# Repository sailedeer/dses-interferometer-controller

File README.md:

# dses-interferometer-controller
A repository for interferometer controller code, hardware, and simulations. 

See dses.science for more information on the Deep Space Exploration Society.

## System Overview

## Hardware
TODO

## Hardware Setup
To view/edit the KiCAD schematic, with KiCAD 6 open, go to Preferences -> Configure Paths, and add a new environment variable called "EWB" that points to dses-interferometer-controller\Hardware\lib.

## Raspberry Pi Setup

Install the 64 bit Raspberry Pi OS with Desktop. Configure the hostname and enable SSH with the right username and password.

``` bash
#Install the PyPy 3.9 Version of Conda Forge: Miniforge3-Linux-aarch64. 
#Use the default install directory, and allow it to initialize the base environment by default.
wget https://github.com/conda-forge/miniforge/releases/latest/download/Mambaforge-pypy3-Linux-aarch64.sh
sudo chmod +x Mambaforge-pypy3-Linux-aarch64.sh
./Mambaforge-pypy3-Linux-aarch64.sh

source ~/.bashrc #this will initialize the base env

mamba update python #update python

mamba create -n radioconda -c conda-forge -c ryanvolz --only-deps radioconda #Install radioconda 

conda activate radioconda

#Blacklist bad drivers
sudo ln -s $CONDA_PREFIX/etc/modprobe.d/rtl-sdr-blacklist.conf /etc/modprobe.d/radioconda-rtl-sdr-blacklist.conf
sudo modprobe -r $(cat $CONDA_PREFIX/etc/modprobe.d/rtl-sdr-blacklist.conf | sed -n -e 's/^blacklist //p')

#Udev rule
sudo ln -s $CONDA_PREFIX/lib/udev/rules.d/rtl-sdr.rules /etc/udev/rules.d/radioconda-rtl-sdr.rules
sudo udevadm control --reload
sudo udevadm trigger

#test the installation (plug in an RTL-SDR)
rtl_test
```

## Simulation Setup
Use Python 3.9.

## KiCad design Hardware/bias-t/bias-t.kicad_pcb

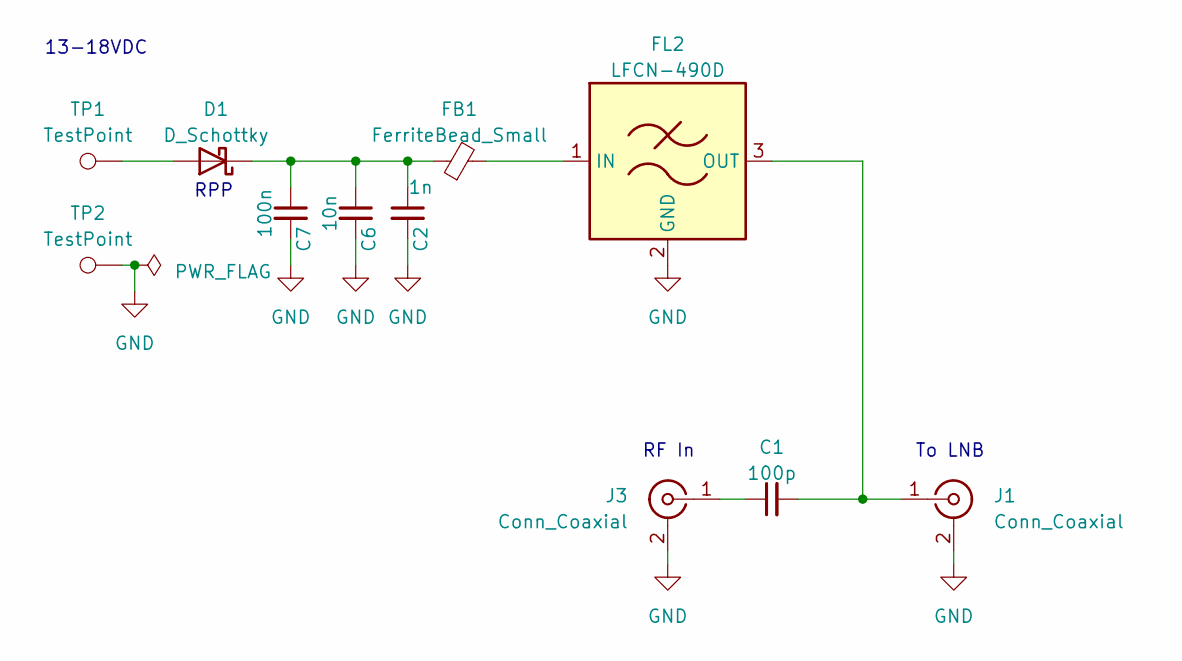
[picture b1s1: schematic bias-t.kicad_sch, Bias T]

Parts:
C1: 100p; C_0603_1608Metric
C2: 1n; C_0603_1608Metric
C6: 10n; C_0603_1608Metric
C7: 100n; C_0603_1608Metric
D1: D_Schottky; D_SOD-123
FB1: FerriteBead_Small; L_0805_2012Metric
FL2: LFCN-490D; Filter_Mini-Circuits_FV1206
J1, J3: Conn_Coaxial; SMA_Samtec_SMA-J-P-X-ST-EM1_EdgeMount
TP1, TP2: TestPoint; TestPoint_THTPad_4.0x4.0mm_Drill2.0mm

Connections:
GND: C2.2, C6.2, C7.2, FL2.2 (GND), FL2.4 (GND), J1.2 (Ext), J3.2 (Ext), TP2.1
unnamed: D1.2 (A), TP1.1
unnamed: C2.1, C6.1, C7.1, D1.1 (K), FB1.1
unnamed: FB1.2, FL2.1 (IN)
unnamed: C1.2, FL2.3 (OUT), J1.1 (In)
unnamed: C1.1, J3.1 (In)

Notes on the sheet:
RF In
To LNB
13-18VDC
RPP

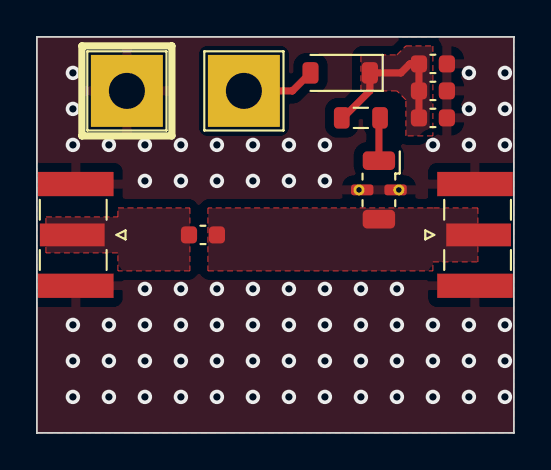
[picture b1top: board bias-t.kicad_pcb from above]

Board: 2 copper layers, 26.5 x 22.0 mm, 11 parts (0 on the bottom side), 6 nets.

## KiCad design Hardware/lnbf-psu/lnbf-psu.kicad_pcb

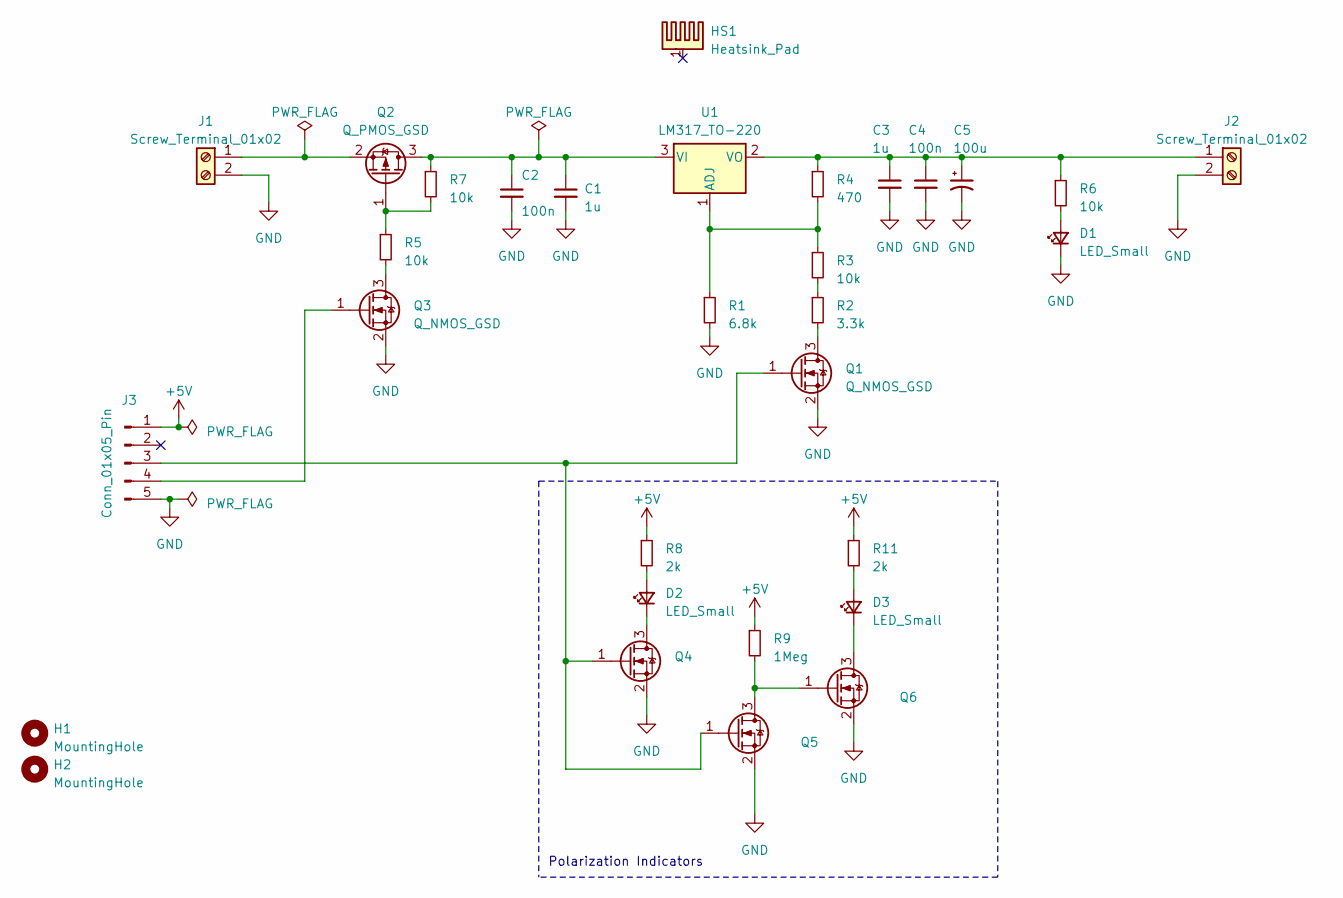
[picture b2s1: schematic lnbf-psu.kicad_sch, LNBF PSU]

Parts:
C1, C3: 1u; C_0805_2012Metric
C2, C4: 100n; C_1206_3216Metric
C5: 100u; CP_Elec_10x10
D1, D2, D3: LED_Small; LED_0805_2012Metric
H1, H2: MountingHole; MountingHole_2.7mm_M2.5
HS1: Heatsink_Pad; TO-220-RS-Heatsink
J1, J2: Screw_Terminal_01x02; TerminalBlock_Phoenix_MKDS-3-2-5.08_1x02_P5.08mm_Horizontal
J3: Conn_01x05_Pin; PinHeader_1x05_P2.54mm_Vertical
Q1, Q3, Q4, Q5, Q6: Q_NMOS_GSD; SOT-23
Q2: Q_PMOS_GSD; TO-252-2
R1: 6.8k; R_0603_1608Metric
R2: 3.3k; R_0603_1608Metric
R3, R5, R6, R7: 10k; R_0603_1608Metric
R4: 470; R_0603_1608Metric
R8, R11: 2k; R_0603_1608Metric
R9: 1Meg; R_0603_1608Metric
U1: LM317_TO-220; TO-220F-3_Horizontal_TabDown

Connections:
+5V: J3.1, R8.1, R9.1, R11.1
GND: C1.2, C2.2, C3.2, C4.2, C5.2, D1.1 (K), J1.2, J2.2, J3.5, Q1.2 (S), Q3.2 (S), Q4.2 (S), Q5.2 (S), Q6.2 (S), R1.2
unnamed: D1.2 (A), R6.2
unnamed: D2.2 (A), R8.2
unnamed: D2.1 (K), Q4.3 (D)
unnamed: D3.2 (A), R11.2
unnamed: D3.1 (K), Q6.3 (D)
unnamed: J1.1, Q2.2 (S)
unnamed: C3.1, C4.1, C5.1, J2.1, R4.1, R6.1, U1.2 (VO)
unnamed: J3.3, Q1.1 (G), Q4.1 (G), Q5.1 (G)
unnamed: J3.4, Q3.1 (G)
unnamed: Q1.3 (D), R2.2
unnamed: C1.1, C2.1, Q2.3 (D), R7.1, U1.3 (VI)
unnamed: Q2.1 (G), R5.1, R7.2
unnamed: Q3.3 (D), R5.2
unnamed: Q5.3 (D), Q6.1 (G), R9.2
unnamed: R2.1, R3.2
unnamed: R1.1, R3.1, R4.2, U1.1 (ADJ)

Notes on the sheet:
Polarization Indicators

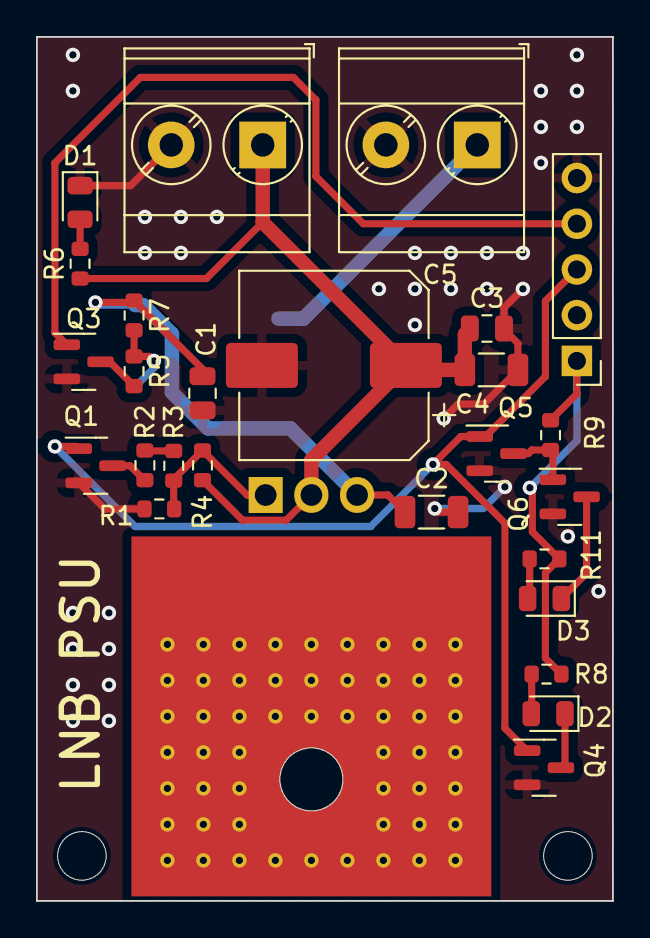
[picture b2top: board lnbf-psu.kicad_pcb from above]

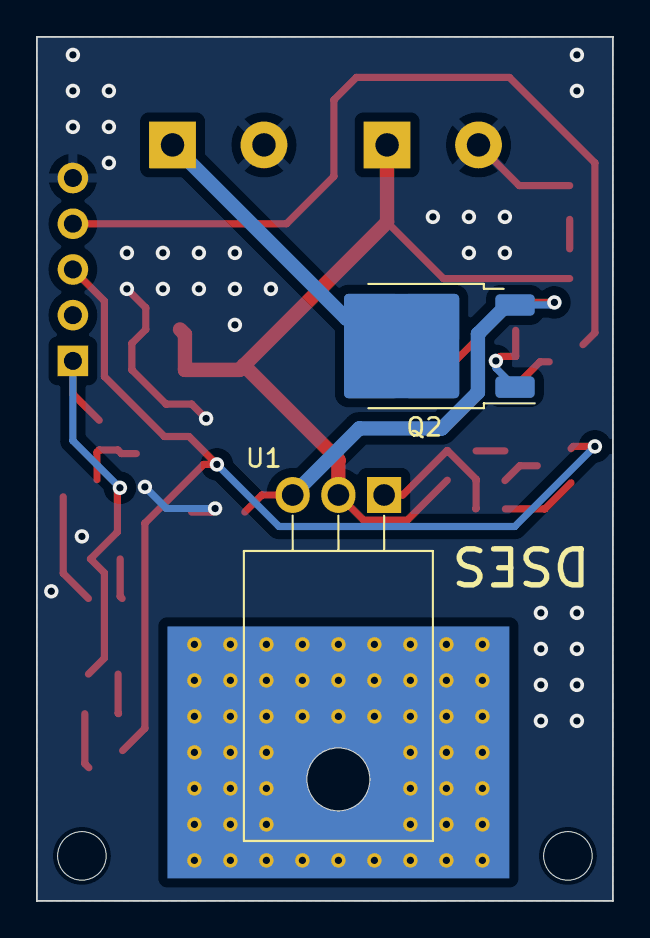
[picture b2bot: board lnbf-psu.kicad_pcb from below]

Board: 2 copper layers, 32.0 x 48.0 mm, 31 parts (2 on the bottom side), 18 nets.

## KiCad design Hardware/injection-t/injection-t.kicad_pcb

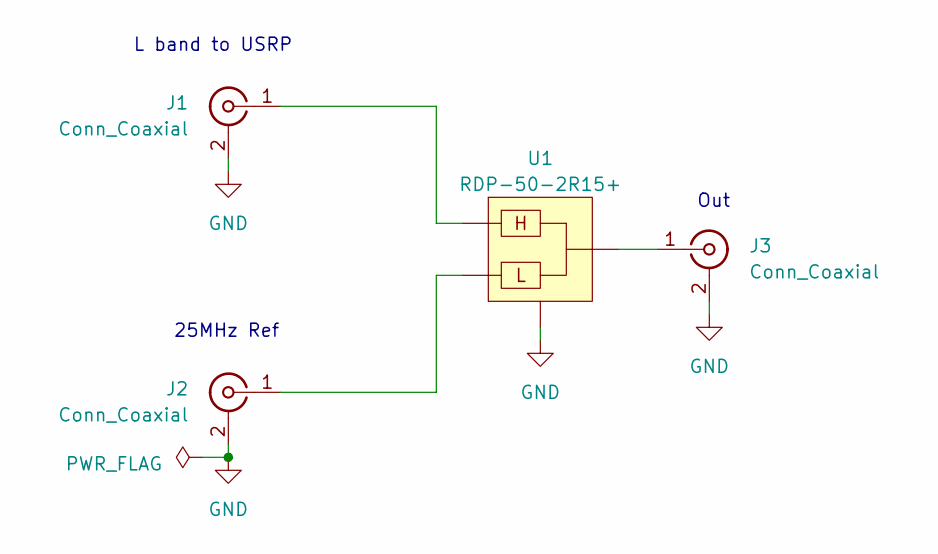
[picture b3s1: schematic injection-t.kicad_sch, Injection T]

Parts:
J1, J2, J3: Conn_Coaxial; SMA_Samtec_SMA-J-P-X-ST-EM1_EdgeMount
U1: RDP-50-2R15+; Mini-Circuits_CK605_LandPatternPL-012

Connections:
GND: J1.2 (Ext), J2.2 (Ext), J3.2 (Ext), U1.1 (GND), U1.3 (GND), U1.4 (GND), U1.5 (GND), U1.6 (GND), U1.7 (GND), U1.8 (GND), U1.9 (GND), U1.11 (GND), U1.12 (GND), U1.13 (GND), U1.15 (GND), U1.16 (GND)
unnamed: J1.1 (In), U1.10 (HI)
unnamed: J2.1 (In), U1.14 (LO)
unnamed: J3.1 (In), U1.2 (COM)

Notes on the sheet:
25MHz Ref
L band to USRP
Out

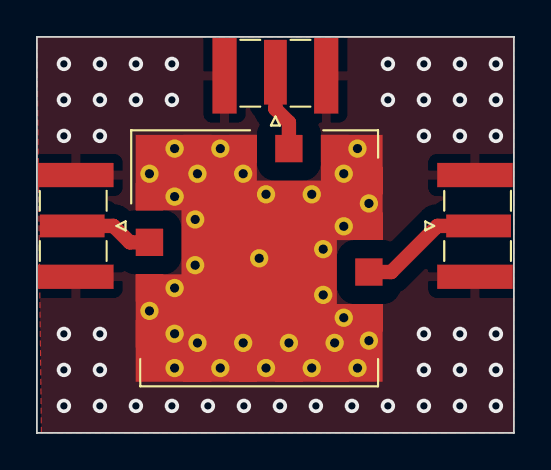
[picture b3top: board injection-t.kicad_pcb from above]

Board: 2 copper layers, 26.5 x 22.0 mm, 4 parts (0 on the bottom side), 4 nets.

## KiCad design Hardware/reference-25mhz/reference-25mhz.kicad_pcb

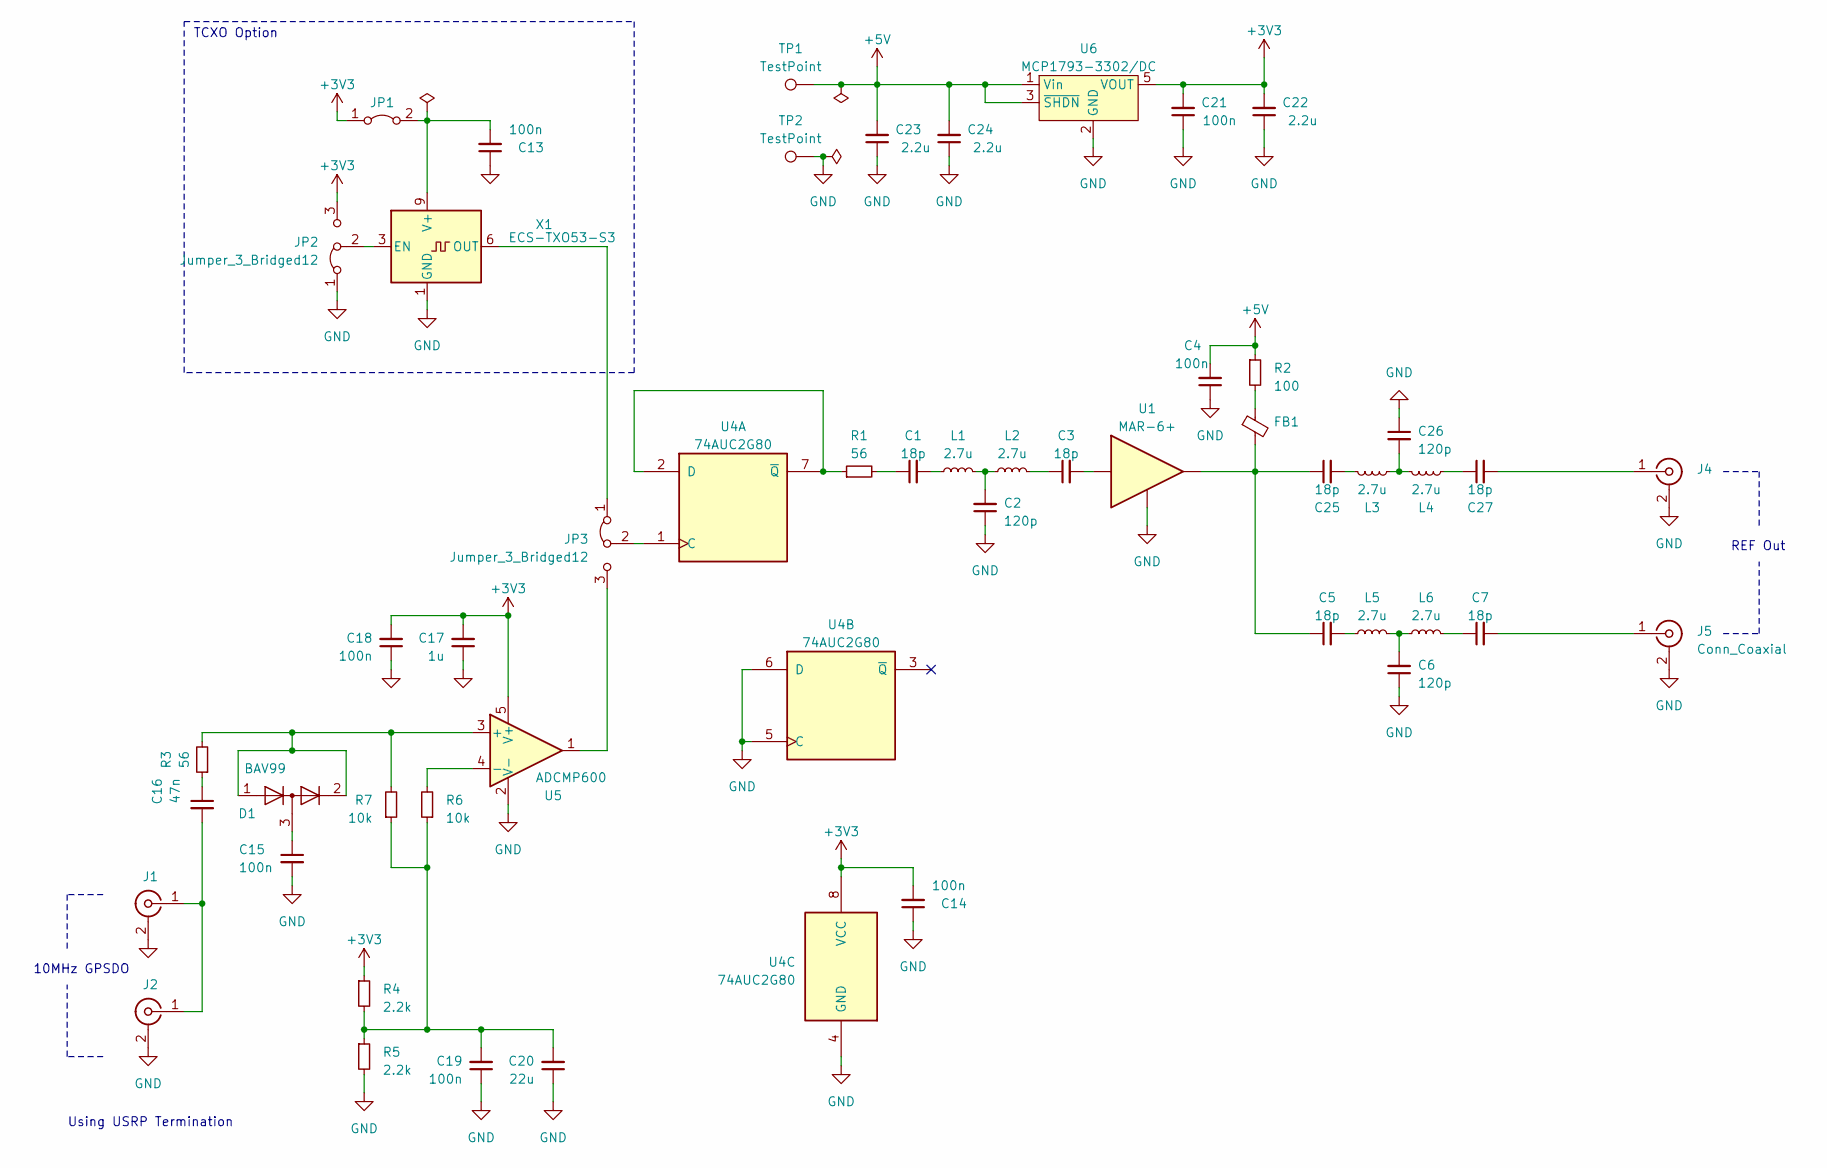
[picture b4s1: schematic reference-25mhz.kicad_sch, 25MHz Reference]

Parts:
C1, C3, C5, C7, C25, C27: 18p; C_0603_1608Metric
C2, C6, C26: 120p; C_0603_1608Metric
C4, C13, C14, C15, C18, C19, C21: 100n; C_1206_3216Metric
C16: 47n; C_0603_1608Metric
C17: 1u; C_0603_1608Metric
C20: 22u; C_0805_2012Metric
C22, C23, C24: 2.2u; C_0603_1608Metric
D1: BAV99; SOT-23
FB1: FerriteBead_Small; L_0805_2012Metric
J1, J2, J4, J5: Conn_Coaxial; SMA_Samtec_SMA-J-P-X-ST-EM1_EdgeMount
JP1: Jumper_2_Bridged; R_0603_1608Metric
JP2: Jumper_3_Bridged12; SolderJumper-3_P1.3mm_Bridged12_Pad1.0x1.5mm
JP3: Jumper_3_Bridged12; SolderJumper-3_P1.3mm_Open_Pad1.0x1.5mm
L1, L2, L3, L4, L5, L6: 2.7u; L_0603_1608Metric
R1, R3: 56; R_0603_1608Metric
R2: 100; R_0603_1608Metric
R4, R5: 2.2k; R_0603_1608Metric
R6, R7: 10k; R_0603_1608Metric
TP1, TP2: TestPoint; TestPoint_THTPad_2.5x2.5mm_Drill1.2mm
U1: MAR-6+; MINICIRCUITS_VV105
U4: 74AUC2G80; VSSOP-8_2.3x2mm_P0.5mm
U5: ADCMP600; SOT-353_SC-70-5
U6: MCP1793-3302/DC; SOT-23-5
X1: ECS-TXO53-S3

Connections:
+3V3: C14.2, C17.2, C18.2, C21.2, C22.2, JP1.1 (A), JP2.3 (B), R4.1, U4.8 (VCC), U5.5 (V+), U6.5 (VOUT)
+5V: C4.2, C23.2, C24.2, R2.1, TP1.1, U6.1 (Vin), U6.3 (~SHDN)
GND: C2.1, C4.1, C6.1, C13.1, C14.1, C15.2, C17.1, C18.1, C19.1, C20.1, C21.1, C22.1, C23.1, C24.1, C26.1, J1.2 (Ext), J2.2 (Ext), J4.2 (Ext), J5.2 (Ext), JP2.1 (A), R5.2, TP2.1, U1.2 (GND), U1.4 (GND), U4.4 (GND), U4.5 (C), U4.6 (D), U5.2 (V-), U6.2 (GND), X1.1 (GND), X1.4 (GND)
unnamed: C13.2, JP1.2 (B), X1.9 (V+)
unnamed: C1.1, R1.2
unnamed: C1.2, L1.1
unnamed: C2.2, L1.2, L2.1
unnamed: C3.1, L2.2
unnamed: C5.2, L5.1
unnamed: C6.2, L5.2, L6.1
unnamed: C7.1, L6.2
unnamed: C15.1, D1.3 (K)
unnamed: C16.1, R3.1
unnamed: C19.2, C20.2, R4.2, R5.1, R6.1, R7.1
unnamed: C25.2, L3.1
unnamed: C26.2, L3.2, L4.1
unnamed: C27.1, L4.2
unnamed: D1.1 (K), D1.2 (A), R3.2, R7.2, U5.3 (+)
unnamed: FB1.1, R2.2
unnamed: C16.2, J1.1 (In), J2.1 (In)
unnamed: C27.2, J4.1 (In)
unnamed: C7.2, J5.1 (In)
unnamed: JP2.2 (C), X1.3 (EN)
unnamed: JP3.1 (A), X1.6 (OUT)
unnamed: JP3.3 (B), U5.1
unnamed: JP3.2 (C), U4.1 (C)
unnamed: C3.2, U1.1 (RFIN)
unnamed: C5.1, C25.1, FB1.2, U1.3 (RFOUT)
unnamed: R1.1, U4.2 (D), U4.7 (~Q)
unnamed: R6.2, U5.4 (-)

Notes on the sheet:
REF Out
Using USRP Termination
10MHz GPSDO
TCXO Option

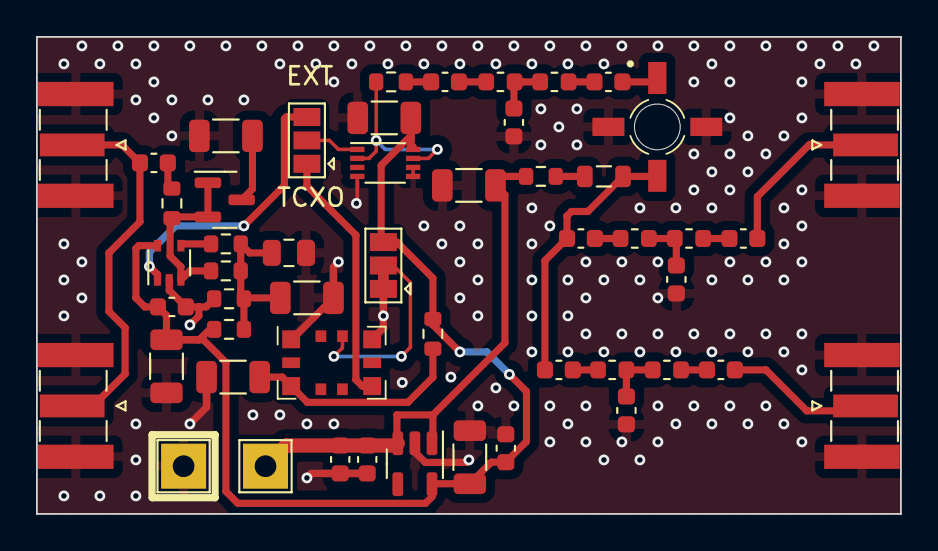
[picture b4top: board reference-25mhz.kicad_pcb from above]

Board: 2 copper layers, 48.0 x 26.5 mm, 51 parts (0 on the bottom side), 30 nets.

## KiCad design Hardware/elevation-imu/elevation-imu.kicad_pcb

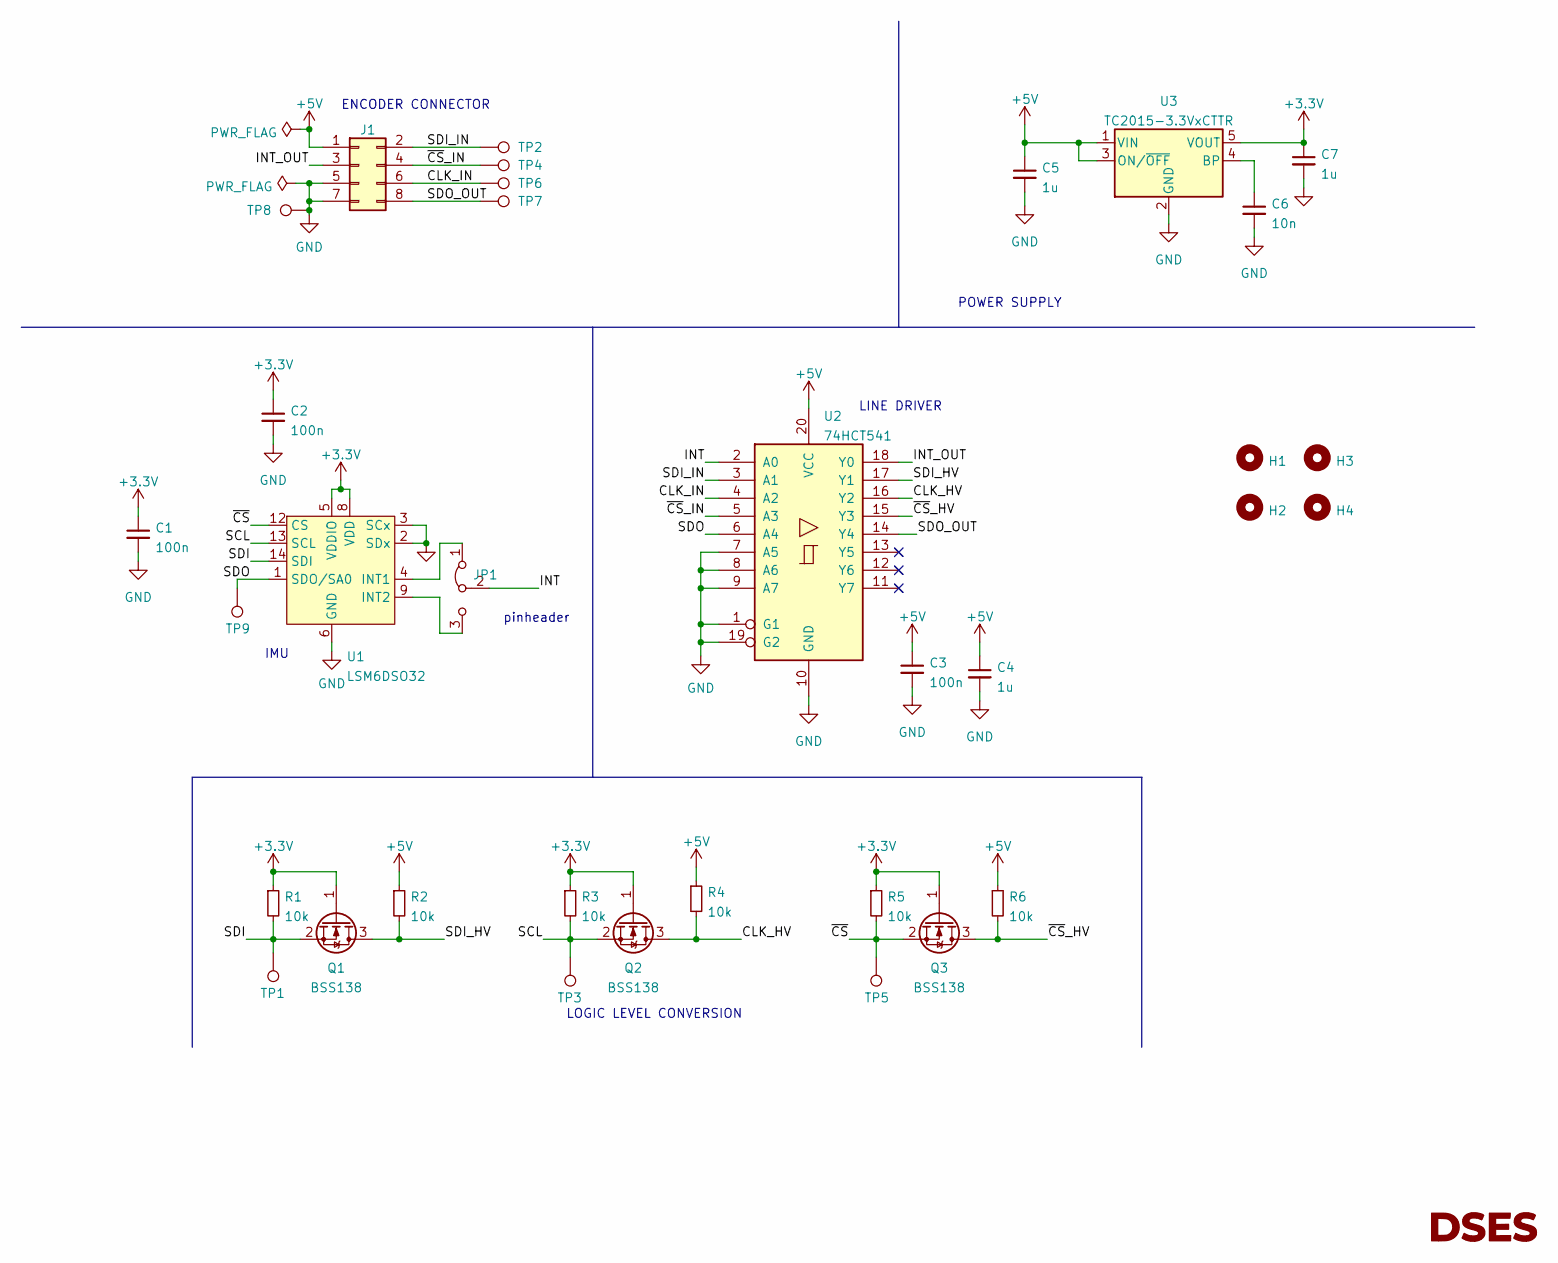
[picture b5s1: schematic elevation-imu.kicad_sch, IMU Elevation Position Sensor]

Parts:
C1, C2, C3: 100n; C_1206_3216Metric
C4, C5, C7: 1u; C_0603_1608Metric
C6: 10n; C_0603_1608Metric
G1: DSES-Logo; dses-logo
H1, H2, H3, H4: MountingHole; MountingHole_3.2mm_M3
J1: Conn_02x04_Odd_Even; RJ45-UPDOWN_P100MIL
JP1: Jumper_3_Bridged12; SolderJumper-3_P1.3mm_Bridged12_Pad1.0x1.5mm_NumberLabels
Q1, Q2, Q3: BSS138; SOT-323_SC-70
R1, R2, R3, R4, R5, R6: 10k; R_0603_1608Metric
TP1, TP2, TP3, TP4, TP5, TP6, TP7, TP8, TP9: TestPoint; TestPoint_THTPad_D1.0mm_Drill0.5mm
U1: LSM6DSO32; Bosch_LGA-14_3x2.5mm_P0.5mm
U2: 74HCT541; TSSOP-20_4.4x6.5mm_P0.65mm
U3: TC2015-3.3VxCTTR; SOT-23-5

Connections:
+3V3: C1.1, C2.1, C7.1, Q1.1 (G), Q2.1 (G), Q3.1 (G), R1.1, R3.1, R5.1, U1.5 (VDDIO), U1.8 (VDD), U3.5 (VOUT)
+5V: C3.1, C4.1, C5.1, J1.1, R2.1, R4.1, R6.1, U2.20 (VCC), U3.1 (VIN), U3.3 (ON/~OFF)
/CLK_HV: Q2.3 (D), R4.2, U2.16 (Y2)
/CLK_IN: J1.6, TP6.1, U2.4 (A2)
/INT: JP1.2 (C), U2.2 (A0)
/INT_OUT: J1.3, U2.18 (Y0)
/SCL: Q2.2 (S), R3.2, TP3.1, U1.13 (SCL)
/SDI: Q1.2 (S), R1.2, TP1.1, U1.14 (SDI)
/SDI_HV: Q1.3 (D), R2.2, U2.17 (Y1)
/SDI_IN: J1.2, TP2.1, U2.3 (A1)
/SDO: TP9.1, U1.1 (SDO/SA0), U2.6 (A4)
/SDO_OUT: J1.8, TP7.1, U2.14 (Y4)
/~CS: Q3.2 (S), R5.2, TP5.1, U1.12 (CS)
/~CS_HV: Q3.3 (D), R6.2, U2.15 (Y3)
/~CS_IN: J1.4, TP4.1, U2.5 (A3)
GND: C1.2, C2.2, C3.2, C4.2, C5.2, C6.2, C7.2, J1.5, J1.7, TP8.1, U1.2 (SDx), U1.3 (SCx), U1.6 (GND), U1.7 (GND), U2.1 (G1), U2.7 (A5), U2.8 (A6), U2.9 (A7), U2.10 (GND), U2.19 (G2), U3.2 (GND)
unnamed: JP1.1 (A), U1.4 (INT1)
unnamed: JP1.3 (B), U1.9 (INT2)
unnamed: C6.1, U3.4 (BP)

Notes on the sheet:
IMU
POWER SUPPLY
LINE DRIVER
pinheader
LOGIC LEVEL CONVERSION
ENCODER CONNECTOR

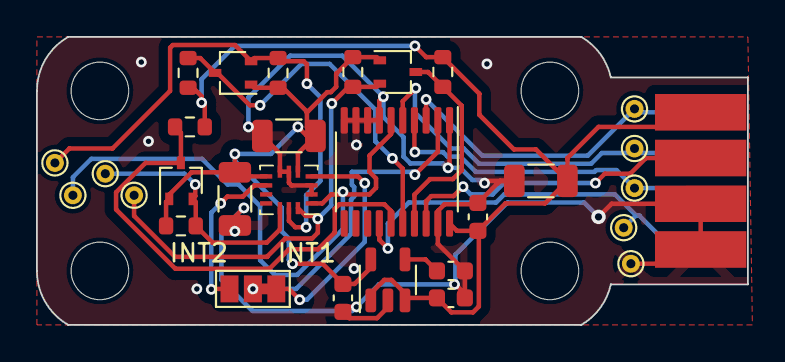
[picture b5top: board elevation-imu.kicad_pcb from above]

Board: 2 copper layers, 39.5 x 16.0 mm, 35 parts (1 on the bottom side), 19 nets.

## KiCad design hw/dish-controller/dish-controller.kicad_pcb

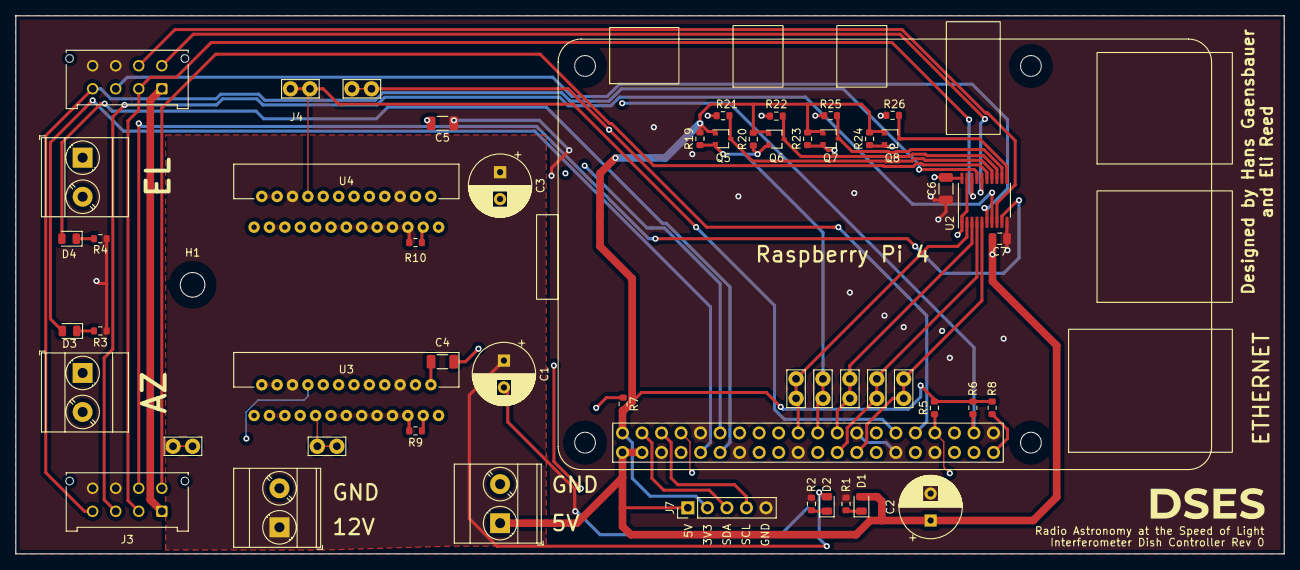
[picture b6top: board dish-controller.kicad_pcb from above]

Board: 4 copper layers, 165.0 x 70.0 mm, 55 parts (0 on the bottom side), 52 nets.

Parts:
C1, C2, C3: 100u; CP_Radial_D8.0mm_P3.50mm
C4, C5, C6: 0.1u; C_1206_3216Metric
C7: 1u; C_0805_2012Metric
D1, D2, D3, D4: LED_Small; LED_0805_2012Metric
G1: DSES-Logo; dses-logo
H1: MountingHole; MountingHole_3.2mm_M3
J1: 12V-IN; TerminalBlock_Phoenix_MKDS-3-2-5.08_1x02_P5.08mm_Horizontal
J2: 5V-IN; TerminalBlock_Phoenix_MKDS-3-2-5.08_1x02_P5.08mm_Horizontal
J3, J4: Encoder_Conn; Molex_Micro-Fit_3.0_43045-0812_2x04_P3.00mm_Vertical
J5: AZ-OUT; TerminalBlock_Phoenix_MKDS-3-2-5.08_1x02_P5.08mm_Horizontal
J6: EL-OUT; TerminalBlock_Phoenix_MKDS-3-2-5.08_1x02_P5.08mm_Horizontal
J7: Conn_01x05_Male; PinHeader_1x05_P2.54mm_Vertical
Q5, Q6, Q7, Q8: BSS138; SOT-323_SC-70
R1: 3.3k; R_0603_1608Metric
R2, R5, R6, R7, R8, R19, R20, R21, R22, R23, R24, R25, R26: 10k; R_0603_1608Metric
R3, R4: 2k; R_0603_1608Metric
R9, R10: 51k; R_0603_1608Metric
TP1, TP2, TP3, TP4, TP5, TP6, TP7, TP8, TP9: TestPoint; TestPoint_Bridge_Pitch2.54mm_Drill1.0mm
U1: raspberry_pi_4
U2: 74HCT541; TSSOP-20_4.4x6.5mm_P0.65mm
U3, U4: TB67H303HG; HZIP25-P-1.00F

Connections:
+3V3: J7.2, Q5.1 (G), Q6.1 (G), Q7.1 (G), Q8.1 (G), R5.2, R6.2, R7.2, R8.2, R19.2, R20.2, R23.2, R24.2, U1.1 (3V3)
+5V: C2.1, C6.2, C7.2, D1.2 (A), J2.1, J3.1, J4.1, J7.1, R21.2, R22.2, R25.2, R26.2, U1.2 (5V), U1.4 (5V), U2.20 (VCC)
+12V: C1.1, C3.1, D2.2 (A), J1.1, U3.6 (VCC), U3.20 (VCC), U4.6 (VCC), U4.20 (VCC)
/A11: R5.1, U1.33 (GPIO13), U3.1 (ALERT1)
/A12: R6.1, U1.37 (GPIO26), U4.1 (ALERT1)
/A21: R7.1, U1.35 (GPIO19), U3.25 (ALERT2)
/A22: R8.1, U1.40 (GPIO21), U4.25 (ALERT2)
/AZ-1: J5.2, U3.12 (OUT1B), U3.16 (OUT1A)
/AZ-2: J5.1, U3.10 (OUT2B), U3.14 (OUT2A)
/CLK: TP5.1, U1.23 (GPIO11), U2.3 (A1)
/CLK_OUT: J3.4, J4.4, U2.17 (Y1)
/EL-1: J6.2, U4.12 (OUT1B), U4.16 (OUT1A)
/EL-2: J6.1, U4.10 (OUT2B), U4.14 (OUT2A)
/EPWM1: Q7.2 (S), R23.1, U1.16 (GPIO23)
/EPWM1_IN: J4.6, U2.8 (A6)
/EPWM2: Q8.2 (S), R24.1, U1.18 (GPIO24)
/EPWM2_IN: J3.6, U2.9 (A7)
/E_~EN: U1.38 (GPIO20), U2.1 (G1), U2.19 (G2)
/GPIO_2: J7.3, U1.3 (GPIO2)
/GPIO_3: J7.4, U1.5 (GPIO3)
/IN11: TP1.1, U1.13 (GPIO27), U3.8 (IN1)
/IN12: TP6.1, U1.29 (GPIO5), U4.8 (IN1)
/IN21: TP2.1, U1.15 (GPIO22), U3.9 (IN2)
/IN22: TP7.1, U1.31 (GPIO6), U4.9 (IN2)
/Logic Level Shift 2/HV1: Q5.3 (D), R21.1, U2.14 (Y4)
/Logic Level Shift 2/HV2: Q6.3 (D), R22.1, U2.13 (Y5)
/Logic Level Shift 2/HV3: Q7.3 (D), R25.1, U2.12 (Y6)
/Logic Level Shift 2/HV4: Q8.3 (D), R26.1, U2.11 (Y7)
/PWM1: U1.36 (GPIO16), U3.22 (PWM)
/PWM2: U1.32 (GPIO12), U4.22 (PWM)
/SDI: TP3.1, U1.19 (GPIO10), U2.2 (A0)
/SDI_OUT: J3.2, J4.2, U2.18 (Y0)
/SDO: Q5.2 (S), Q6.2 (S), R19.1, R20.1, TP4.1, U1.21 (GPIO9)
/SDO_IN1: J4.3, U2.6 (A4)
/SDO_IN2: J3.3, U2.7 (A5)
/STB1: U1.7 (GPIO4), U3.7 (STBY)
/STB2: U1.11 (GPIO17), U4.7 (STBY)
/~CS1: TP8.1, U1.24 (GPIO8), U2.4 (A2)
/~CS1_OUT: J4.5, U2.16 (Y2)
/~CS2: TP9.1, U1.26 (GPIO7), U2.5 (A3)
/~CS2_OUT: J3.5, U2.15 (Y3)
GND: C1.2, C2.2, C3.2, C4.1, C5.1, C6.1, C7.1, J1.2, J2.2, J3.7, J3.8, J4.7, J4.8, J7.5, R1.1, R2.2, R3.2, R4.1, R9.1, R10.1, U1.6 (GND), U1.9 (GND), U1.14 (GND), U1.20 (GND), U1.25 (GND), U1.30 (GND), U1.34 (GND), U1.39 (GND), U2.10 (GND), U3.2 (SGND), U3.3 (SELECT), U3.4 (TEST1), U3.5 (VREF), U3.11 (RSB), U3.13 (PGNDB), U3.15 (RSA), U3.17 (PGNDA), U3.18 (TEST2), U3.19 (TEST3), U3.21 (TEST4), U4.2 (SGND), U4.3 (SELECT), U4.4 (TEST1), U4.5 (VREF), U4.11 (RSB), U4.13 (PGNDB), U4.15 (RSA), U4.17 (PGNDA), U4.18 (TEST2), U4.19 (TEST3), U4.21 (TEST4)
unnamed: C4.2, U3.24 (Vreg)
unnamed: C5.2, U4.24 (Vreg)
unnamed: D1.1 (K), R1.2
unnamed: D2.1 (K), R2.1
unnamed: D3.1 (K), R3.1
unnamed: D3.2 (A), U1.10 (GPIO15)
unnamed: D4.1 (K), R4.2
unnamed: D4.2 (A), U1.12 (GPIO18)
unnamed: R9.2, U3.23 (OSC)
unnamed: R10.2, U4.23 (OSC)

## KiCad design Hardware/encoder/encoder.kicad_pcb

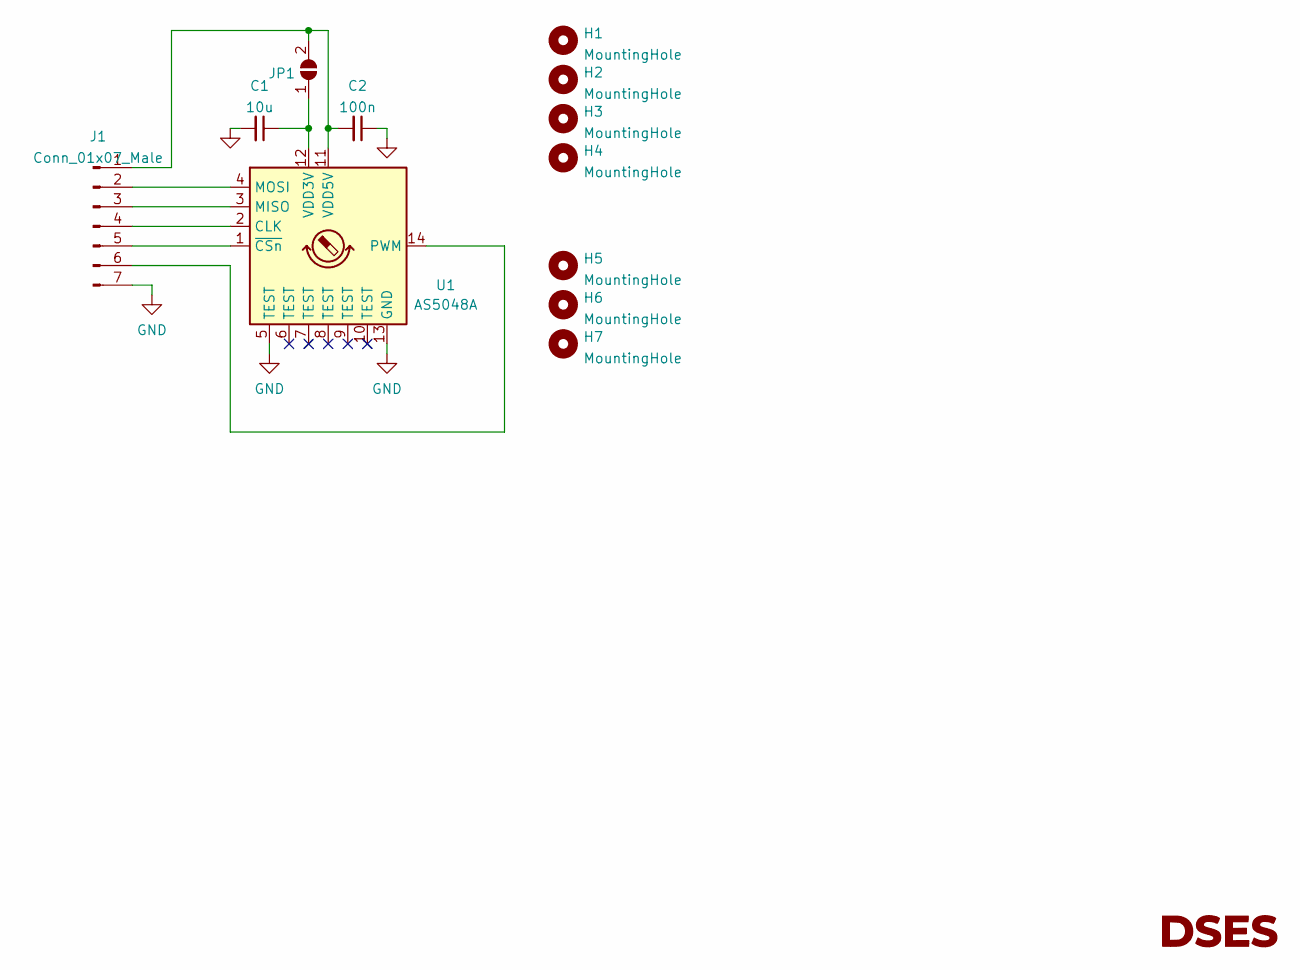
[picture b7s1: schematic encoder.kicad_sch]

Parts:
C1: 10u; C_0805_2012Metric
C2: 100n; C_1206_3216Metric
G1: DSES-Logo; dses-logo
H1, H2, H3, H4, H5, H6, H7: MountingHole; MountingHole_3.2mm_M3
J1: Conn_01x07_Male; PinHeader_1x07_P2.54mm_Vertical
JP1: SolderJumper_2_Open; SolderJumper-2_P1.3mm_Open_Pad1.0x1.5mm
U1: AS5048A; TSSOP-14_4.4x5mm_P0.65mm

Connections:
GND: C1.2, C2.1, J1.7, U1.5 (TEST), U1.13 (GND)
unnamed: C1.1, JP1.1 (A), U1.12 (VDD3V)
unnamed: C2.2, J1.1, JP1.2 (B), U1.11 (VDD5V)
unnamed: J1.2, U1.4 (MOSI)
unnamed: J1.3, U1.3 (MISO)
unnamed: J1.4, U1.2 (CLK)
unnamed: J1.5, U1.1 (~CSn)
unnamed: J1.6, U1.14 (PWM)

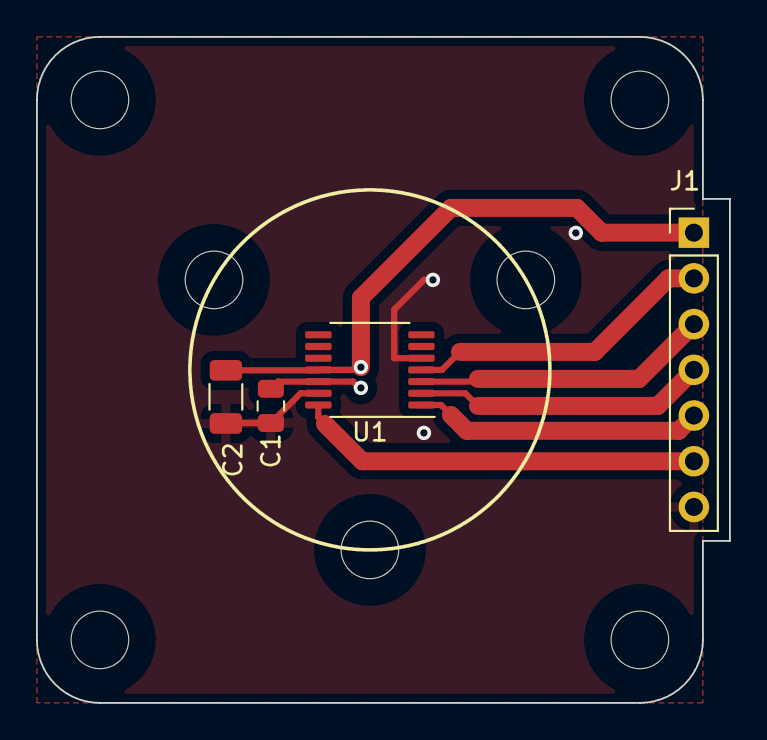
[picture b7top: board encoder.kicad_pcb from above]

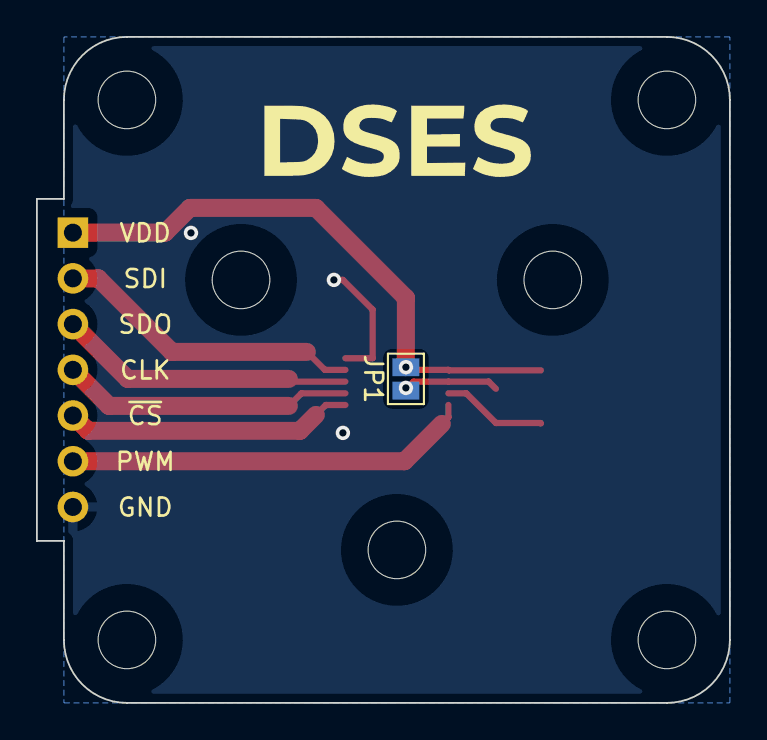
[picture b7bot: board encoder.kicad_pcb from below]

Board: 2 copper layers, 38.5 x 37.0 mm, 13 parts (2 on the bottom side), 8 nets.

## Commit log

2022-01-17 Configure project
    Create folders for hardware and simulation. Start hardware schematic
2022-01-17 Remove ignored files
    Forgot to add a .gitignore, removing all the files that should be ignored
2022-01-18 Add pseudorandom signals
    In simulation, added the ability to generate pseudorandom, band-limited, and "continuous" signals for simulating the outputs of astronomical sources.
2022-01-18 Create encoder
    COTS encoders are too expensive, so we are creating our own.
2022-01-19 Add documentation folder
    Added photo documentation and linked it into the README
2022-01-19 Fix README.md
    HTML images were not displayed
2022-01-19 Dish Controller ERC Pass
2022-01-20 Dish Control: DRC Pass
    Floorplanning and routing for dish control PCB complete
2022-01-21 Dish Controller: Update 3D Model
    Added models for the raspberry pi and heatsinks.
2022-01-21 Dish Controller: Fix 3d model colors
    Changed pi 4 model to igs
2022-01-21 Dish Controller: Added I2C header
2022-01-21 Dish Controller: Plot
2022-01-21 Project: Add PCB 3D images
2022-01-21 Project: Add hardware photos to README
2022-01-22 E-IMU: Add Elevation IMU Schematic
2022-01-22 E-IMU: Floorplanning and layout
2022-02-05 Elevation-IMU: Update CAM
2022-02-05 Encoder: Add encoder test
2022-02-10 Dish Controller: Create initial motor driver firmware
    Created a firmware folder and a first draft python class for controlling the TB67H303
2022-02-10 Project: Update .gitignore
    Remove python files and .swp files
2022-02-10 Project: remove swap files and __pycache__ folder
    These files were previously added to the .gitignore
2022-02-10 Dish Controller: Fix motor driver and motor tests
    Also added LED test
2022-02-11 EIMU: Fix disconnected SCL
    This commit fixes a mistake where SCL and SCK were not connected.
2022-02-11 Project: Add Images
2022-02-12 IMU Driver: Add acceleration read functionality
    Added and tested acceleration read from IMU.
2022-02-13 System: Add Motion Control Demo
    Added a python script for driving the motor to a set location with a bang-bang controller
2022-02-22 initial commit of imu_client
2022-02-22 added mqtt diagram
2022-02-22 Added mqtt picture to README
2022-02-22 fixing broken git
2022-03-03 started implementing basic mqtt interface
2022-03-05 wrote basic multithreaded pub/sub if client with canned data
2022-03-05 initial skeleton for server
2022-03-05 added dependencies
2022-03-05 tested and working with mosquitto clients
2022-03-05 fixed issue with exiting while asleep
2022-03-05 fixed potential race condition
2022-03-30 started linux drivers
2022-04-13 Simple kernel drivers
2022-04-24 some updates to drivers
2022-04-24 updates for testing
2022-07-29 getting back up to speed
2022-09-13 Add some lines
2022-09-13 Move folder structure around
2022-09-13 Moved folders around some more
2023-05-27 Added W1MX Test Setup Data
2023-06-02 Firmware Dump
2023-06-02 Reorganized, cleaned up, added trapezoidal controller
2023-06-25 Add 64 bit requirement to readme
2023-06-25 Add intereferometer radio hardware
2023-06-25 Add Pi setup to ReadMe
2023-07-06 Add polarization switch script
